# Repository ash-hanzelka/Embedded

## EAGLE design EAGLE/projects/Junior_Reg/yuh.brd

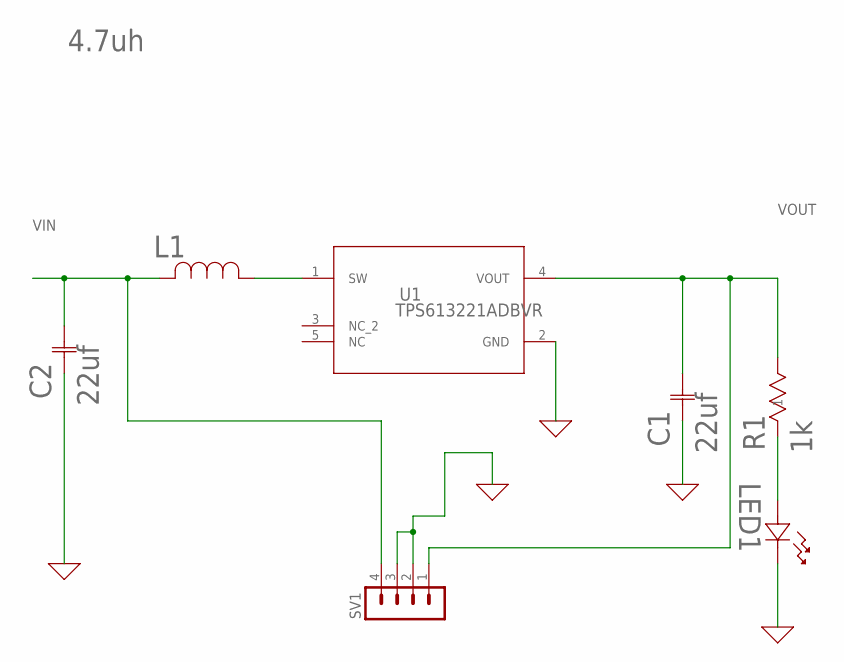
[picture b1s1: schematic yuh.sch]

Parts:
C1, C2: 22uf; CAP_CL21_SAM
L1: 4.7uh; IND_LQM18PXXXXFRX_MUR
LED1: LED_BS75000_WRE
R1: 1k; RES_RC1206_YAG
SV1: MA04-1
U1: TPS613221ADBVR; DBV0005A_N

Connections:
0: C1.1, C2.1, LED1.1, SV1.2, SV1.3, U1.2 (GND)
unnamed: L1.1, U1.1 (SW)
unnamed: LED1.2, R1.1
VIN: C2.2, L1.2, SV1.4
VOUT: C1.2, R1.2, SV1.1, U1.4 (VOUT)

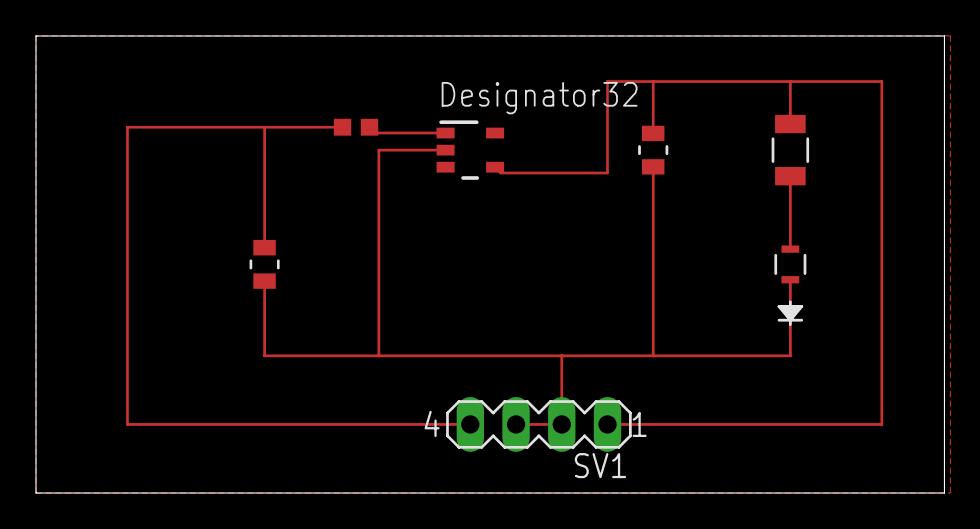
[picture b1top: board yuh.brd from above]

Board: 2 copper layers, 50.5 x 25.4 mm, 7 parts (0 on the bottom side), 5 nets.

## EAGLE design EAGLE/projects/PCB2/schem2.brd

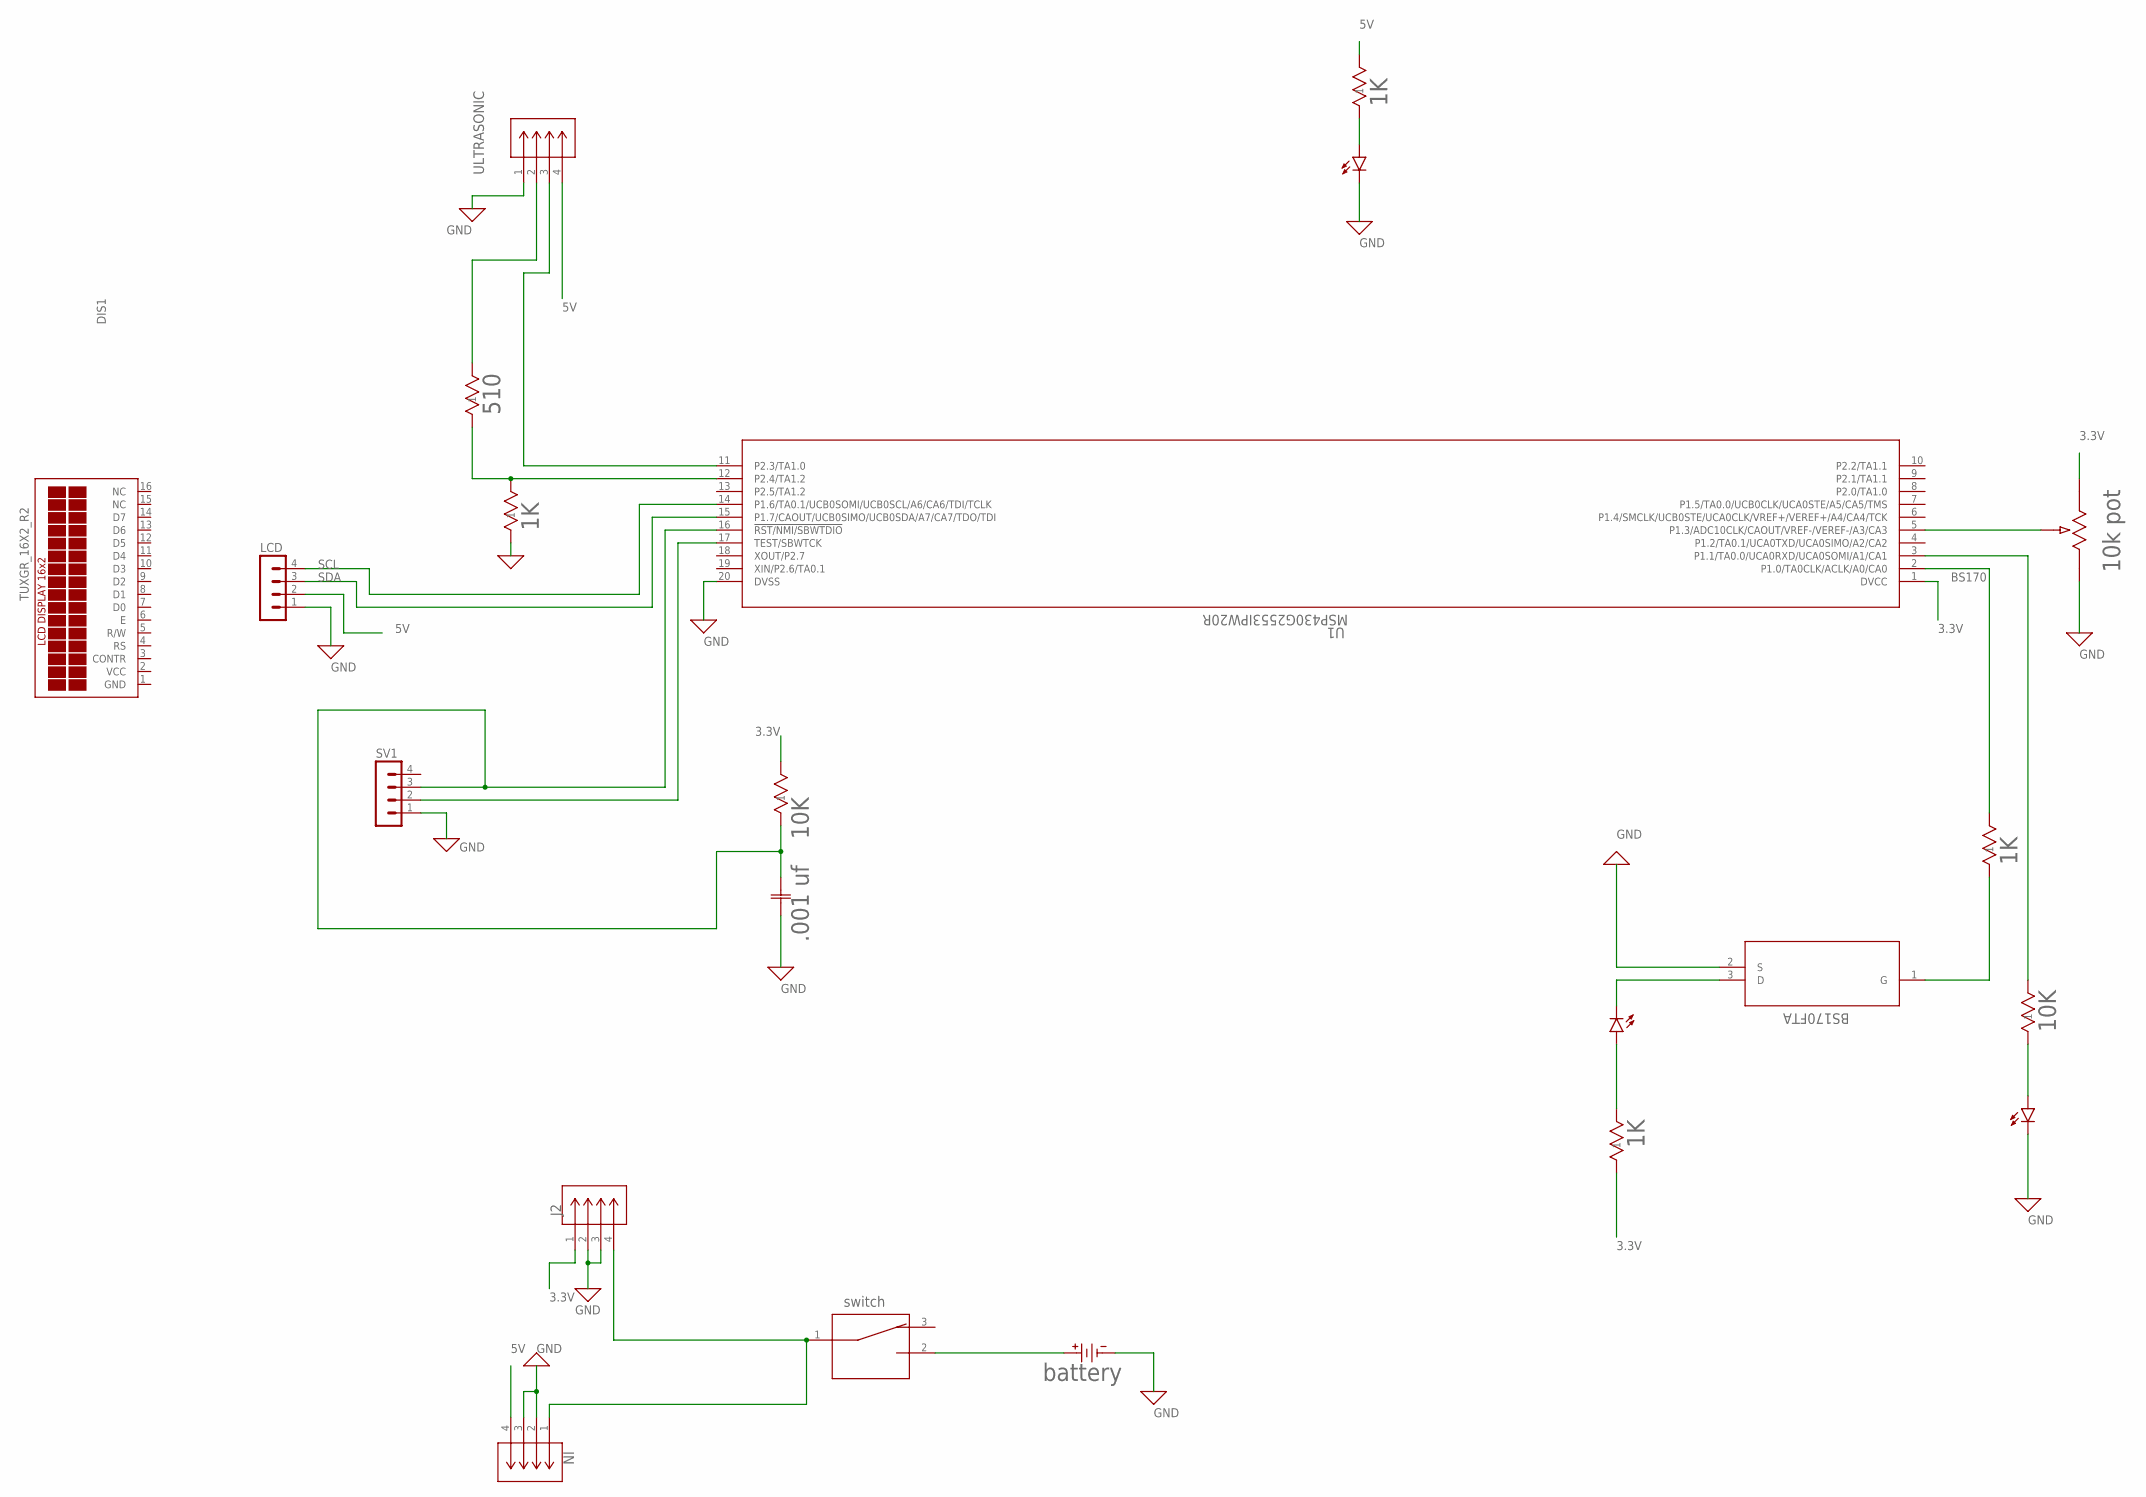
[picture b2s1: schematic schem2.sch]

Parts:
B1: battery; 2462RB_KEY
C1: .001 uf; CAP_1206_B_WAL
DIS1: TUXGR_16X2_R2
IN: SSW-104-01-T-S; CON4_1X4_TU_SSQ
J2: SSW-104-01-T-S; CON4_1X4_TU_SSQ
LCD: MA04-1
LED1, LED2, LED5R: LEDCHIPLED_0805; CHIPLED_0805
R1: 510; STA_RMCF1206_STP
R2, R8: 10K; RC1206N_YAG
R3, R5REG, R6, R7: 1K; RES_RC1206_YAG
R4: 10k pot; POT_3362P
SV1: MA04-1
SW1: switch; 09.03201_EAO
U1: MSP430G2553IPW20R; PW20
U$1: BS170FTA; SOT-23_DIO
ULTRASONIC: SSW-104-01-T-S; CON4_1X4_TU_SSQ

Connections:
0: R3.1
3.3V: J2.1, R2.2, R4.3, R6.1, U1.1 (DVCC)
5V: IN.4, LCD.2, R5REG.2, ULTRASONIC.4
BS170: R7.2, U1.2 (P1.0/TA0CLK/ACLK/A0/CA0)
GND: B1.1, C1.1, DIS1.1 (GND), IN.2, IN.3, J2.2, J2.3, LCD.1, LED2.C, LED5R.C, R4.1, SV1.1, U1.20 (DVSS), U$1.2 (S), ULTRASONIC.1
IN: IN.1, J2.4, SW1.1
unnamed: U1.11 (P2.3/TA1.0), ULTRASONIC.3
unnamed: R1.1, R3.2, U1.12 (P2.4/TA1.2)
unnamed: R1.2, ULTRASONIC.2
unnamed: R4.2, U1.5 (P1.3/ADC10CLK/CAOUT/VREF-/VEREF-/A3/CA3)
unnamed: R7.1, U$1.1 (G)
unnamed: LED1.C, U$1.3 (D)
unnamed: LED1.A, R6.2
unnamed: R8.2, U1.3 (P1.1/TA0.0/UCA0RXD/UCA0SOMI/A1/CA1)
unnamed: LED2.A, R8.1
unnamed: SV1.2, U1.17 (TEST/SBWTCK)
unnamed: C1.2, R2.1, SV1.3, U1.16 (!RST/NMI/SBWTDIO)
unnamed: LED5R.A, R5REG.1
SCL: LCD.4, U1.14 (P1.6/TA0.1/UCB0SOMI/UCB0SCL/A6/CA6/TDI/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)
SDA: LCD.3, U1.15 (P1.7/CAOUT/UCB0SIMO/UCB0SDA/A7/CA7/TDO/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)
VCC: DIS1.2 (VCC)
_: B1.2, SW1.2

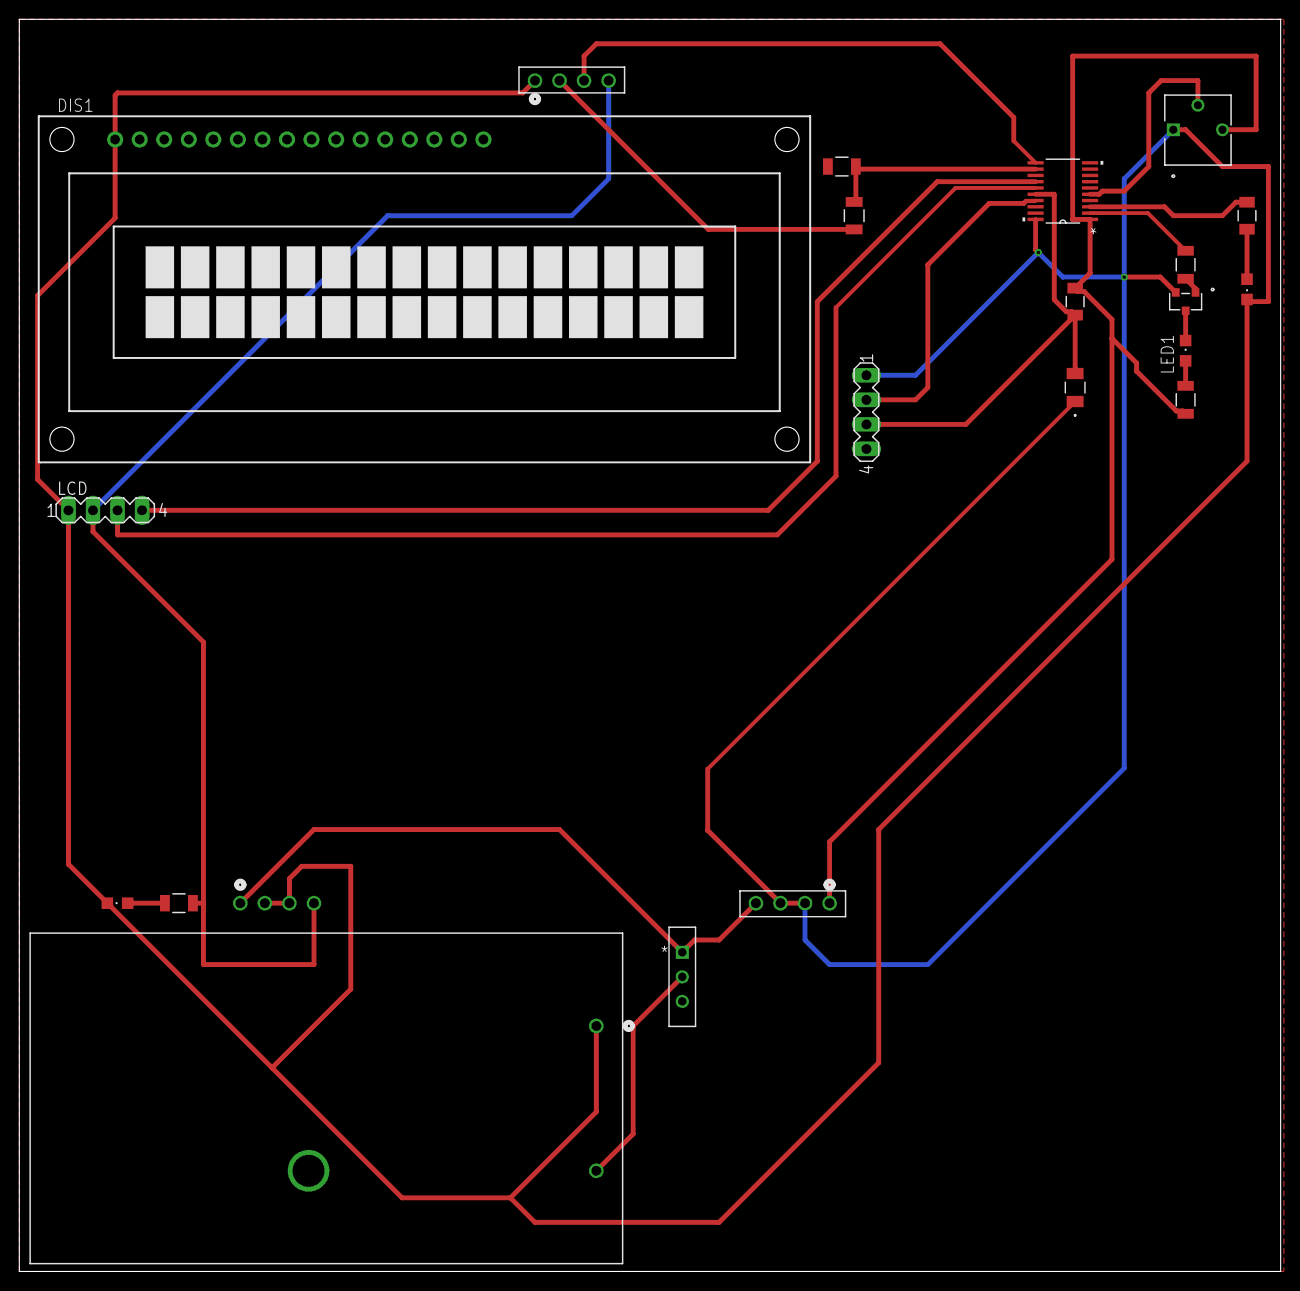
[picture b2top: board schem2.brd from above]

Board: 2 copper layers, 130.5 x 129.5 mm, 22 parts (1 on the bottom side), 20 nets.

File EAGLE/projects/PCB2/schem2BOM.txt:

Partlist exported from /Users/ashleyhanzelka/Documents/EAGLE/projects/PCB2/schem2.sch at 6/19/24 5:23 PM

Part       Value             Device            Package          Description                                                                  COPYRIGHT                                                MANUFACTURER_PART_NUMBER MF MFR_NAME                MPN OC_FARNELL OC_NEWARK POPULARITY TYPE          
B1         battery           2462RB            2462RB_KEY                                                                                    Copyright (C) 2024 Ultra Librarian. All rights reserved. 2462RB                      Keystone Electronics                                                      
C1         .001 uf           1206B473K500CT    CAP_1206_B_WAL                                                                                Copyright (C) 2024 Ultra Librarian. All rights reserved. 1206B473K500CT              Walsin                                                                    
DIS1       TUXGR_16X2_R2     TUXGR_16X2_R2     TUXGR_16X2_R2    Tuxgraphics LCD display 16x2 characters reflective, without background light                                                                                                                  unknown    unknown   5                        
IN         SSW-104-01-T-S    SSW-104-01-T-S    CON4_1X4_TU_SSQ                                                                               Copyright (C) 2024 Ultra Librarian. All rights reserved. SSW-104-01-T-S              Samtec Inc                                                                
J2         SSW-104-01-T-S    SSW-104-01-T-S    CON4_1X4_TU_SSQ                                                                               Copyright (C) 2024 Ultra Librarian. All rights reserved. SSW-104-01-T-S              Samtec Inc                                                                
LCD                          MA04-1            MA04-1           PIN HEADER                                                                                                                                                                                    unknown    unknown   41                       
LED1                         LEDCHIPLED_0805   CHIPLED_0805     LED                                                                                                                                                                                                                52                       
LED2                         LEDCHIPLED_0805   CHIPLED_0805     LED                                                                                                                                                                                                                52                       
LED5R                        LEDCHIPLED_0805   CHIPLED_0805     LED                                                                                                                                                                                                                52                       
R1         510               RMCF1206JT510R    STA_RMCF1206_STP                                                                              Copyright (C) 2024 Ultra Librarian. All rights reserved. RMCF1206JT510R              Stackpole International                                                   
R2         10K               RC1206FR-0710KL   RC1206N_YAG                                                                                   Copyright (C) 2024 Ultra Librarian. All rights reserved. RC1206FR-0710KL             Yageo                                                                     
R3         1K                RC1206FR-071KL    RES_RC1206_YAG                                                                                Copyright (C) 2024 Ultra Librarian. All rights reserved. RC1206FR-071KL              Yageo                                                                     
R4         10k pot           3362P-1-103LF     POT_3362P                                                                                     Copyright (C) 2024 Ultra Librarian. All rights reserved. 3362P-1-103LF               Bourns Electronics                                                        
R5REG      1K                RC1206FR-071KL    RES_RC1206_YAG                                                                                Copyright (C) 2024 Ultra Librarian. All rights reserved. RC1206FR-071KL              Yageo                                                                     
R6         1K                RC1206FR-071KL    RES_RC1206_YAG                                                                                Copyright (C) 2024 Ultra Librarian. All rights reserved. RC1206FR-071KL              Yageo                                                                     
R7         1K                RC1206FR-071KL    RES_RC1206_YAG                                                                                Copyright (C) 2024 Ultra Librarian. All rights reserved. RC1206FR-071KL              Yageo                                                                     
R8         10K               RC1206FR-0710KL   RC1206N_YAG                                                                                   Copyright (C) 2024 Ultra Librarian. All rights reserved. RC1206FR-0710KL             Yageo                                                                     
SV1                          MA04-1            MA04-1           PIN HEADER                                                                                                                                                                                    unknown    unknown   41                       
SW1        switch            09.03201.02       09.03201_EAO                                                                                  Copyright (C) 2024 Ultra Librarian. All rights reserved. 09.03201.02                 EAO                                                         Slide Switches
U$1        BS170FTA          BS170FTA          SOT-23_DIO                                                                                                                                                                                                                                                   
U1         MSP430G2553IPW20R MSP430G2553IPW20R PW20                                                                                          Copyright (C) 2024 Ultra Librarian. All rights reserved. MSP430G2553IPW20R           Texas Instruments                                                         
ULTRASONIC SSW-104-01-T-S    SSW-104-01-T-S    CON4_1X4_TU_SSQ                                                                               Copyright (C) 2024 Ultra Librarian. All rights reserved. SSW-104-01-T-S              Samtec Inc

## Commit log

2025-11-06 Create file
2025-11-06 PCB Jr. Design - EAGLE
2025-11-06 Embedded Labs Folder
2025-11-07 Labs 1-3
2025-11-07 Labs 4 & 5
2025-11-07 Labs 6-9
2025-11-07 All labs
2025-11-11 all arduino folder proj.s

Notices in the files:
parts and their libraries:
COPYRIGHT: Copyright (C) 2024 Ultra Librarian. All rights reserved.
